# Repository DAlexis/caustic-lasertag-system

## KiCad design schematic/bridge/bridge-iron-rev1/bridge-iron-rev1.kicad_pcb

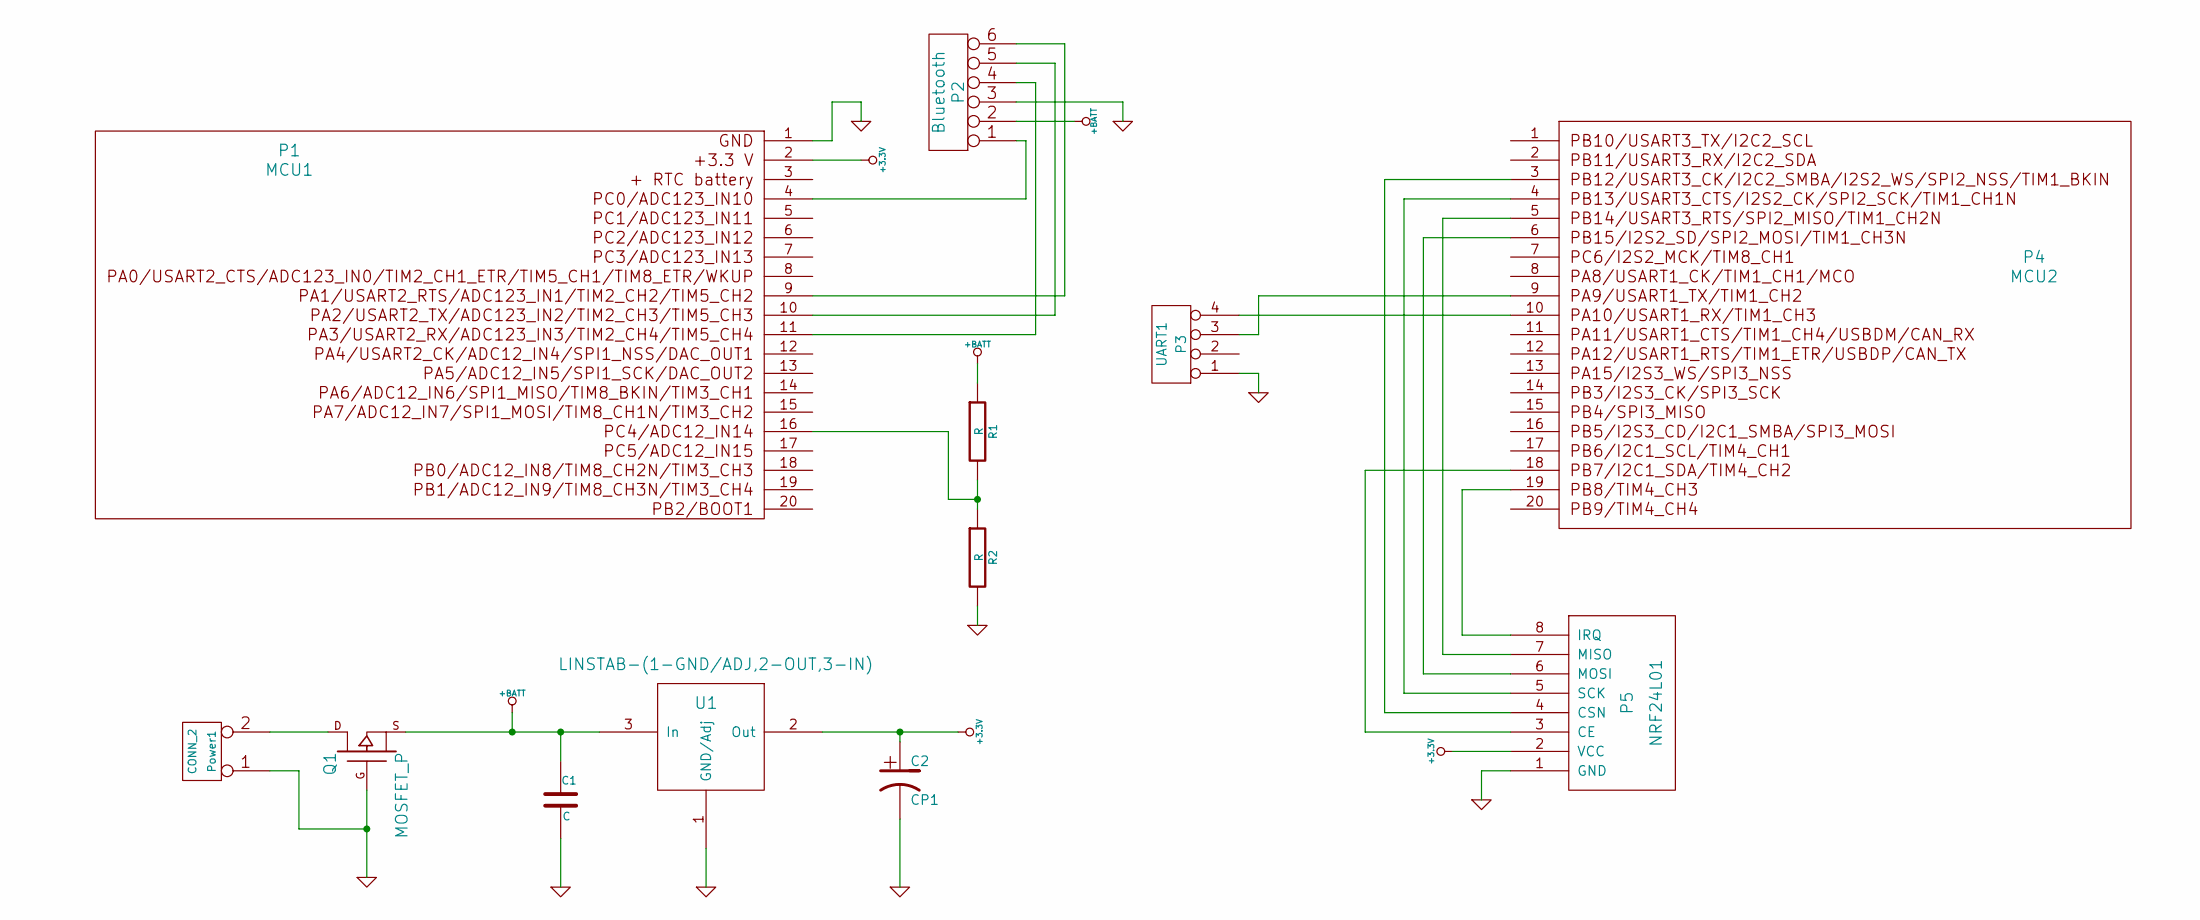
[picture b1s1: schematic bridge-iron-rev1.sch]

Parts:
C1: C
C2: CP1
P1: MCU1
P2: Bluetooth
P3: UART1
P4: MCU2
P5: NRF24L01
Power1: CONN_2
Q1: MOSFET_P
R1, R2: R
U1: LINSTAB-(1-GND/ADJ,2-OUT,3-IN)

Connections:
+3.3V: C2.1, P1.2, P5.2 (VCC), U1.2 (Out)
+BATT: C1.1, P2.2, Q1.S, R1.1, U1.3 (In)
GND: C1.2, C2.2, P1.1, P2.3, P3.1, P5.1 (GND), Power1.1, Q1.G, R2.2, U1.1 (GND/Adj)
unnamed: P4.18, P5.3 (CE)
unnamed: P3.3, P4.9
unnamed: P3.4, P4.10
unnamed: P4.4, P5.5 (SCK)
unnamed: P4.6, P5.6 (MOSI)
unnamed: P4.5, P5.7 (MISO)
unnamed: P4.19, P5.8 (IRQ)
unnamed: P4.3, P5.4 (CSN)
unnamed: P1.9, P2.6
unnamed: P1.4, P2.1
unnamed: Power1.2 (PM), Q1.D
unnamed: P1.11, P2.4
unnamed: P1.10, P2.5
unnamed: P1.16, R1.2, R2.1

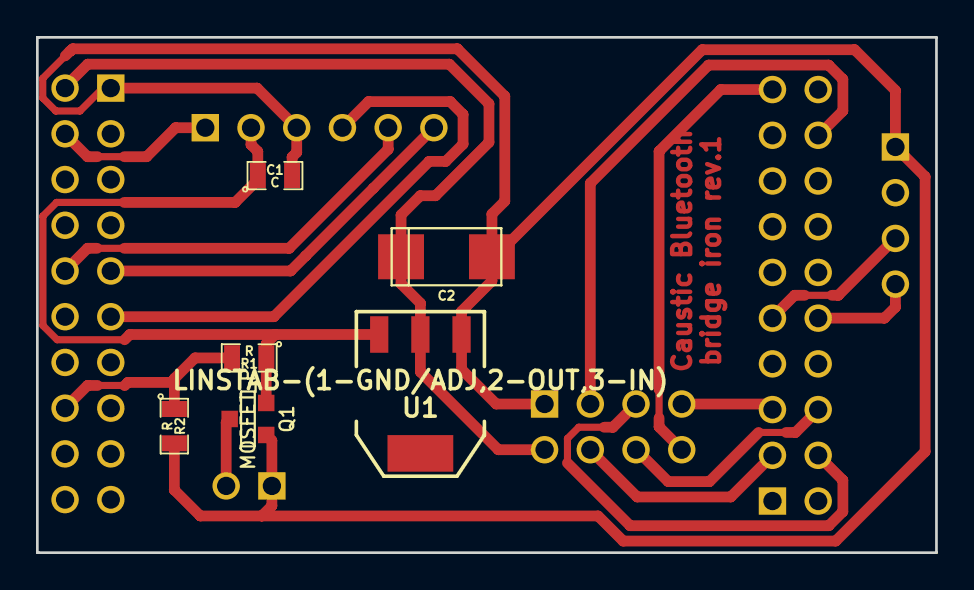
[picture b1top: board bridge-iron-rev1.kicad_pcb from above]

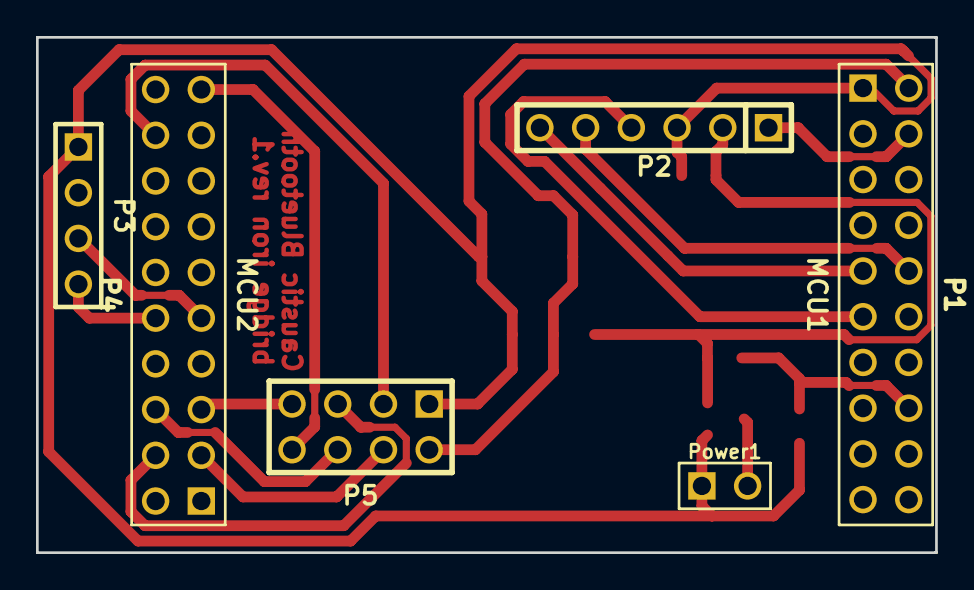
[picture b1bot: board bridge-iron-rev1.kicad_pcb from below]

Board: 2 copper layers, 50.0 x 28.6 mm, 12 parts (6 on the bottom side), 17 nets.

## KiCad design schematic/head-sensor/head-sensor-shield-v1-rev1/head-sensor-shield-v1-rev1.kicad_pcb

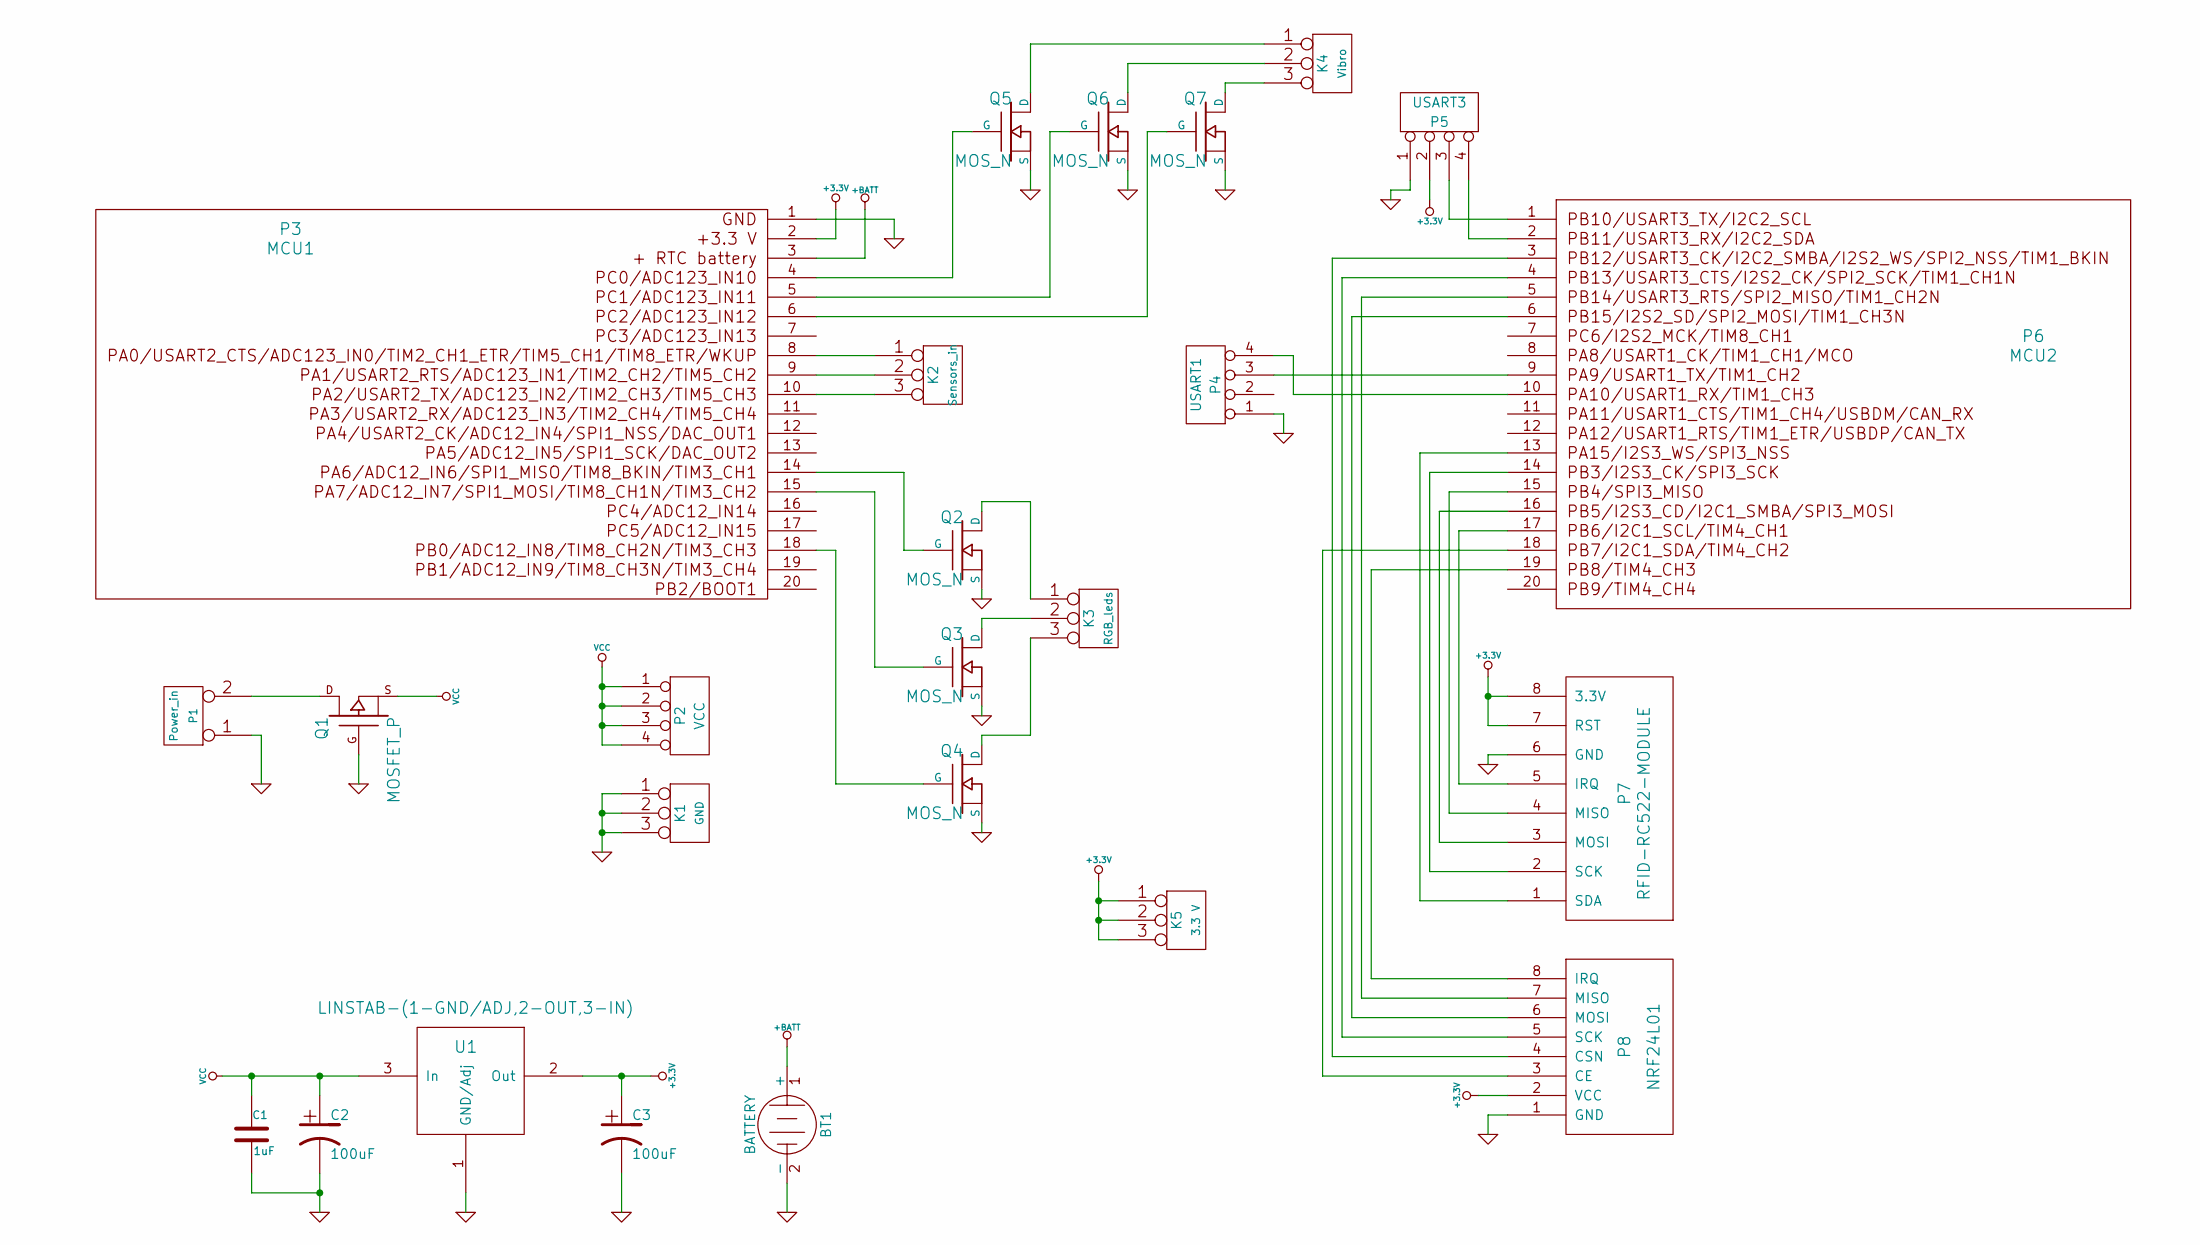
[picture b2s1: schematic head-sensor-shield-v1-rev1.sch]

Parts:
BT1: BATTERY
C1: 1uF
C2, C3: 100uF
K1: GND
K2: Sensors_in
K3: RGB_leds
K4: Vibro
K5: 3.3 V
P1: Power_in
P2: VCC
P3: MCU1
P4: USART1
P5: USART3
P6: MCU2
P7: RFID-RC522-MODULE
P8: NRF24L01
Q1: MOSFET_P
Q2, Q3, Q4, Q5, Q6, Q7: MOS_N
U1: LINSTAB-(1-GND/ADJ,2-OUT,3-IN)

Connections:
+3.3V: C3.1, K5.1, K5.2 (PM), K5.3, P3.2, P5.2, P7.7 (RST), P7.8 (3.3V), P8.2 (VCC), U1.2 (Out)
+BATT: BT1.1 (+), P3.3
GND: BT1.2 (-), C1.2, C2.2, C3.2, K1.1, K1.2 (PM), K1.3, P1.1, P3.1, P4.1, P5.1, P7.6 (GND), P8.1 (GND), Q1.G, Q2.S, Q3.S, Q4.S, Q5.S, Q6.S, Q7.S, U1.1 (GND/Adj)
unnamed: P3.6, Q7.G
unnamed: K4.2 (PM), Q6.D
unnamed: K4.3, Q7.D
unnamed: K4.1, Q5.D
unnamed: P3.5, Q6.G
unnamed: P3.4, Q5.G
unnamed: P3.18, Q4.G
unnamed: P3.15, Q3.G
unnamed: K2.1, P3.8
unnamed: K2.3, P3.10
unnamed: K2.2 (PM), P3.9
unnamed: P5.4, P6.2
unnamed: P5.3, P6.1
unnamed: P1.2 (PM), Q1.D
unnamed: P3.14, Q2.G
unnamed: K3.2 (PM), Q3.D
unnamed: K3.3, Q4.D
unnamed: K3.1, Q2.D
unnamed: P6.17, P7.5 (IRQ)
unnamed: P6.13, P7.1 (SDA)
unnamed: P6.14, P7.2 (SCK)
unnamed: P6.16, P7.3 (MOSI)
unnamed: P6.15, P7.4 (MISO)
unnamed: P6.19, P8.8 (IRQ)
unnamed: P6.18, P8.3 (CE)
unnamed: P6.6, P8.6 (MOSI)
unnamed: P6.5, P8.7 (MISO)
unnamed: P6.4, P8.5 (SCK)
unnamed: P6.3, P8.4 (CSN)
unnamed: P4.3, P6.9
unnamed: P4.4, P6.10
VCC: C1.1, C2.1, P2.1, P2.2, P2.3, P2.4, Q1.S, U1.3 (In)

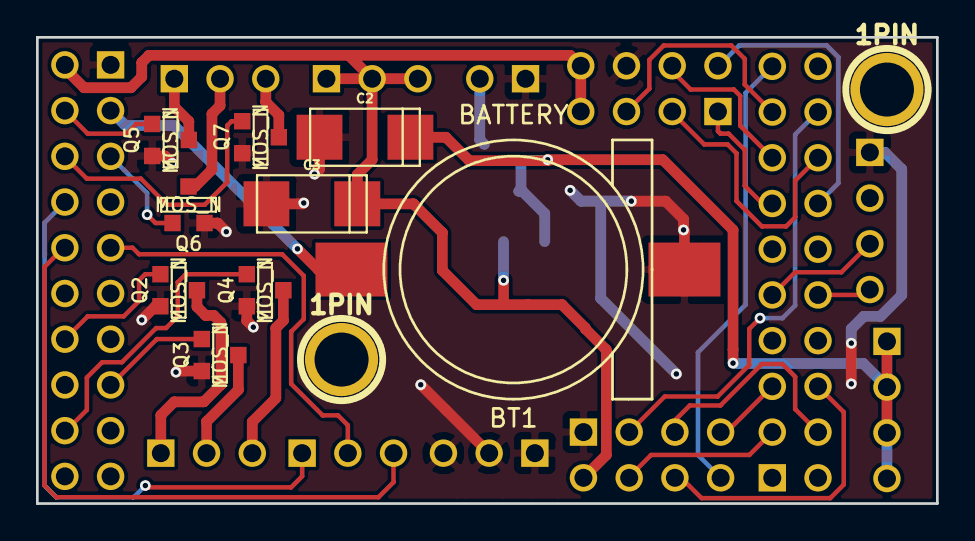
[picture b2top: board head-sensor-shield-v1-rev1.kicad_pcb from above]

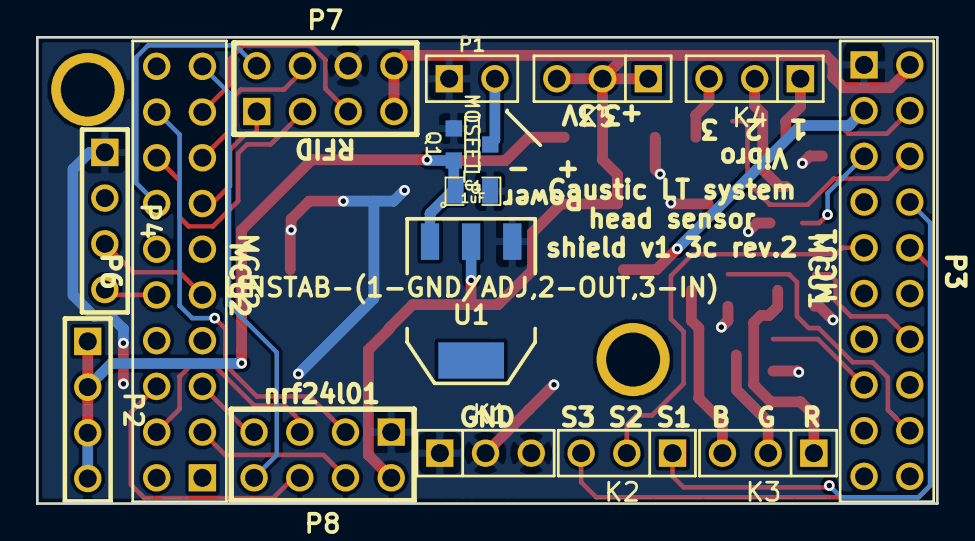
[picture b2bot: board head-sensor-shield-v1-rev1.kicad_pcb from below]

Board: 2 copper layers, 50.0 x 25.9 mm, 26 parts (15 on the bottom side), 33 nets.

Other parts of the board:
1PIN, 1PIN#2: P***; 1pin
